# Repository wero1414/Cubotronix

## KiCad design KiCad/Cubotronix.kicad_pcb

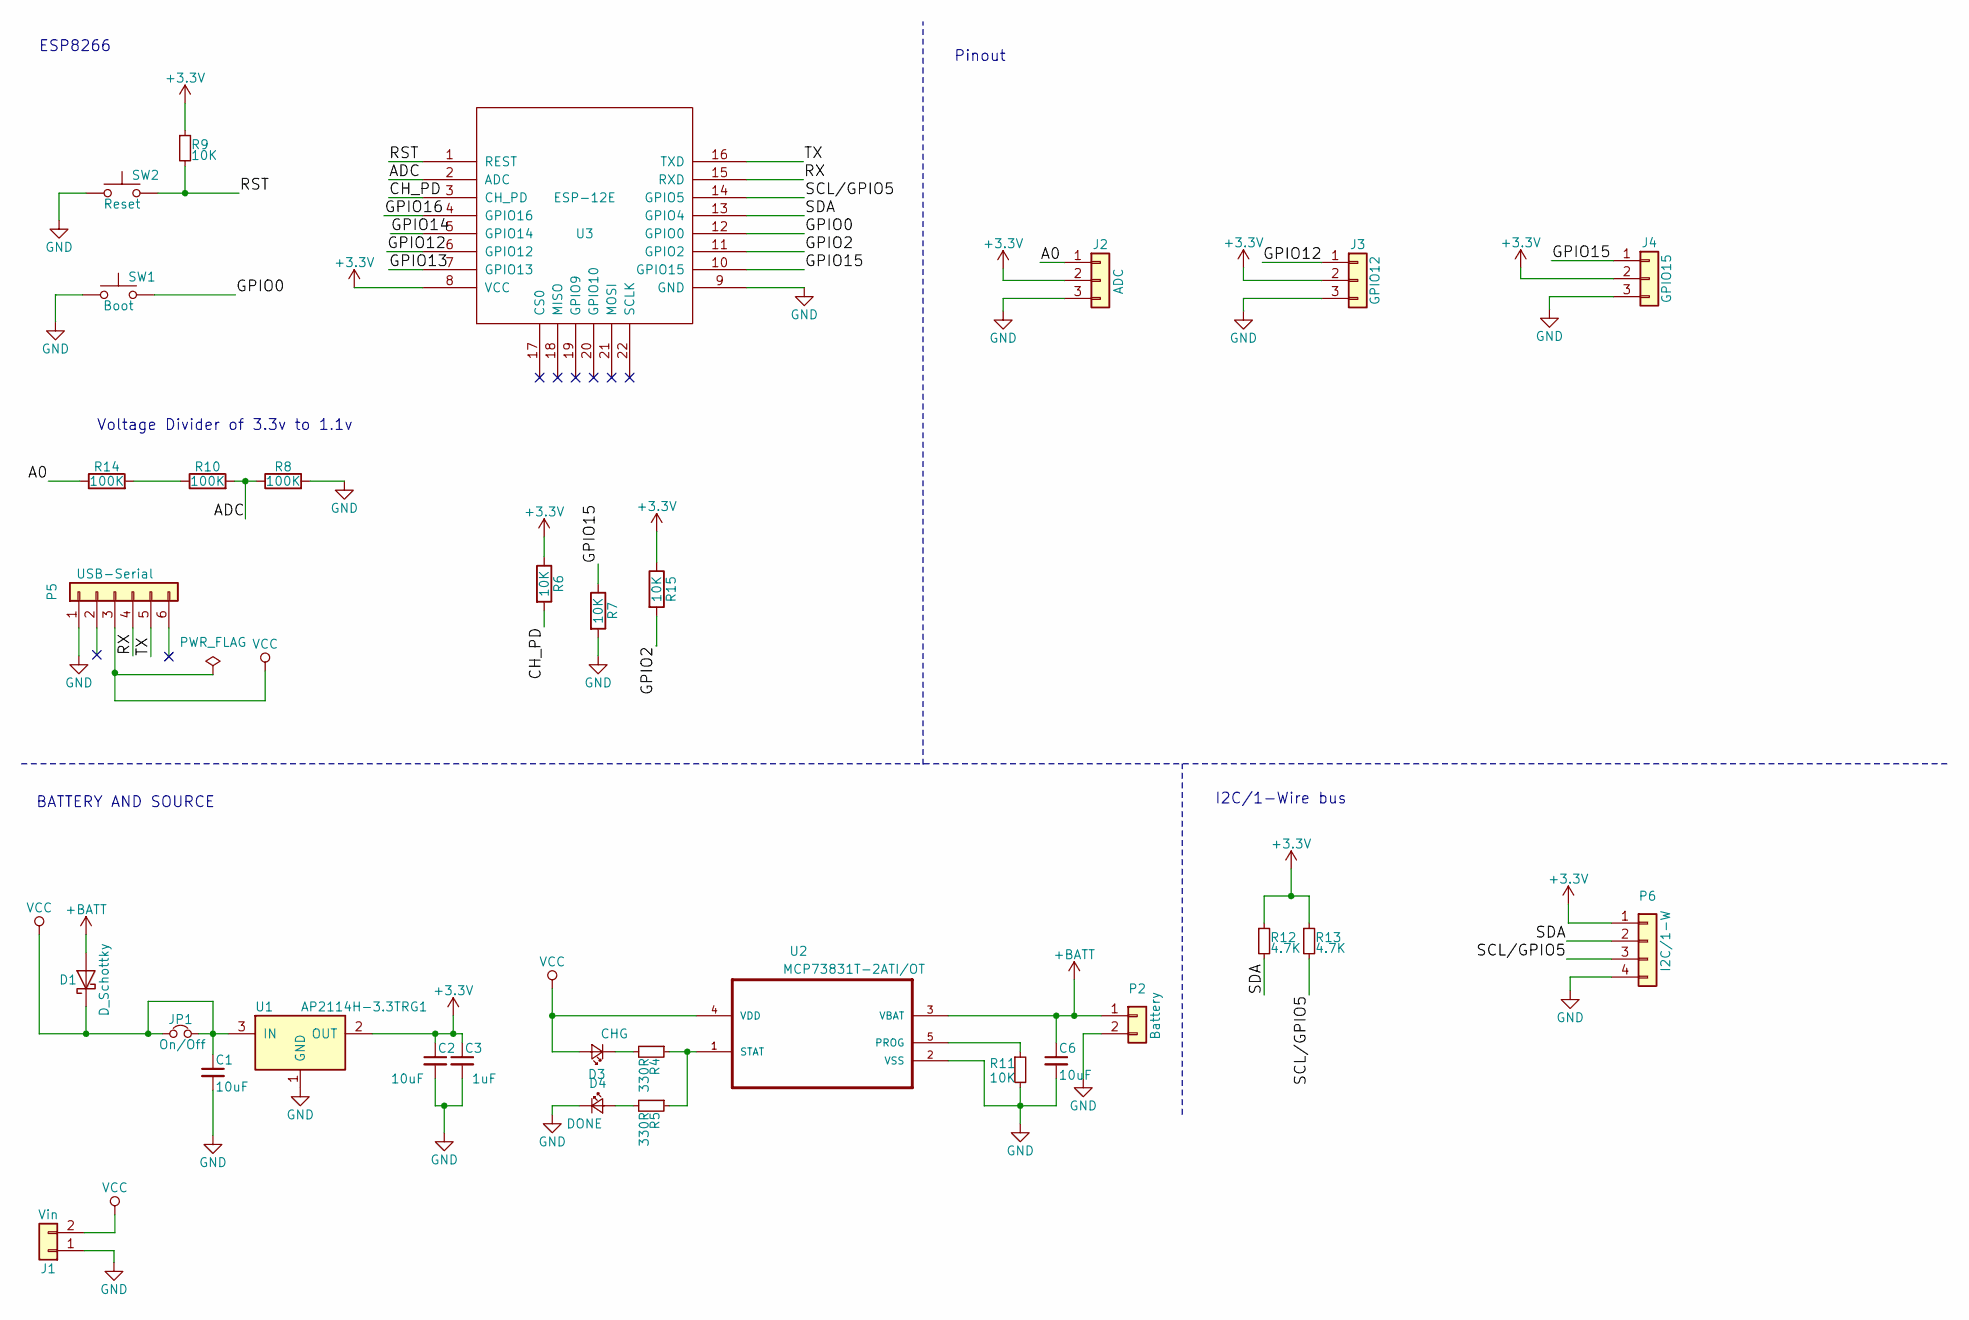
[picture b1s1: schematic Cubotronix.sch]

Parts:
C1, C2, C6: 10uF; C_0805_HandSoldering
C3: 1uF; C_0805_HandSoldering
D1: D_Schottky; SOD-123
D3: CHG; LED_0805
D4: DONE; LED_0805
J1: Vin; Pin_Header_Straight_1x02_Pitch2.54mm
J2: ADC; Pin_Header_Straight_1x03_Pitch2.54mm
J3: GPIO12; Pin_Header_Straight_1x03_Pitch2.54mm
J4: GPIO15; Pin_Header_Straight_1x03_Pitch2.54mm
JP1: On/Off; Pin_Header_Straight_1x02_Pitch2.54mm
P2: Battery; Pin_Header_Straight_1x02_Pitch2.54mm
P5: USB-Serial; Pin_Header_Straight_1x06_Pitch2.54mm
P6: I2C/1-W; Pin_Header_Straight_1x04_Pitch2.54mm
R4, R5: 330R; R_0805_HandSoldering
R6, R7, R9, R11, R15: 10K; R_0805_HandSoldering
R8, R10, R14: 100K; R_0805_HandSoldering
R12, R13: 4.7K; R_0805_HandSoldering
SW1: Boot; SW_SPST_B3U-1000P
SW2: Reset; SW_SPST_B3U-1000P
U1: AP2114H-3.3TRG1; SOT-223-3Lead_TabPin2
U2: MCP73831T-2ATI/OT; SOT-23-5
U3: ESP-12E; ESP-12E_SMD

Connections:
+3V3: C2.1, C3.1, J2.2, J3.2, J4.2, P6.1, R6.1, R9.1, R12.1, R13.1, R15.1, U1.2 (OUT), U3.8 (VCC)
+BATT: C6.1, D1.2 (A), P2.1, U2.3 (VBAT)
/A0: J2.1, R14.1
/ADC: R8.1, R10.2, U3.2 (ADC)
/CH_PD: R6.2, U3.3 (CH_PD)
/GPIO0: SW1.2, U3.12 (GPIO0)
/GPIO2: R15.2, U3.11 (GPIO2)
/GPIO12: J3.1, U3.6 (GPIO12)
/GPIO13: U3.7 (GPIO13)
/GPIO14: U3.5 (GPIO14)
/GPIO15: J4.1, R7.1, U3.10 (GPIO15)
/GPIO16: U3.4 (GPIO16)
/RST: R9.2, SW2.2, U3.1 (REST)
/RX: P5.4, U3.15 (RXD)
/SCL/GPIO5: P6.3, R13.2, U3.14 (GPIO5)
/SDA: P6.2, R12.2, U3.13 (GPIO4)
/TX: P5.5, U3.16 (TXD)
GND: C1.2, C2.2, C3.2, C6.2, D4.1 (K), J1.1, J2.3, J3.3, J4.3, P2.2, P5.1, P6.4, R7.2, R8.2, R11.2, SW1.1, SW2.1, U1.1 (GND), U2.2 (VSS), U3.9 (GND)
unnamed: D3.1 (K), R4.2
unnamed: D4.2 (A), R5.2
unnamed: R4.1, R5.1, U2.1 (STAT)
unnamed: R10.1, R14.2
unnamed: R11.1, U2.5 (PROG)
VCC: C1.1, D1.1 (K), D3.2 (A), J1.2, JP1.1, JP1.2, P5.3, U1.3 (IN), U2.4 (VDD)

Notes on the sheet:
ESP8266
BATTERY AND SOURCE
Voltage Divider of 3.3v to 1.1v
I2C/1-Wire bus
Pinout

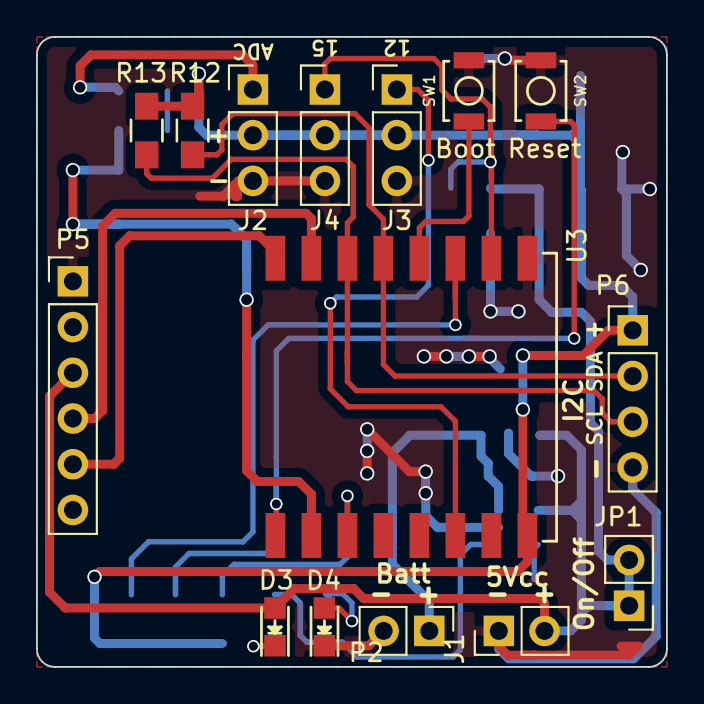
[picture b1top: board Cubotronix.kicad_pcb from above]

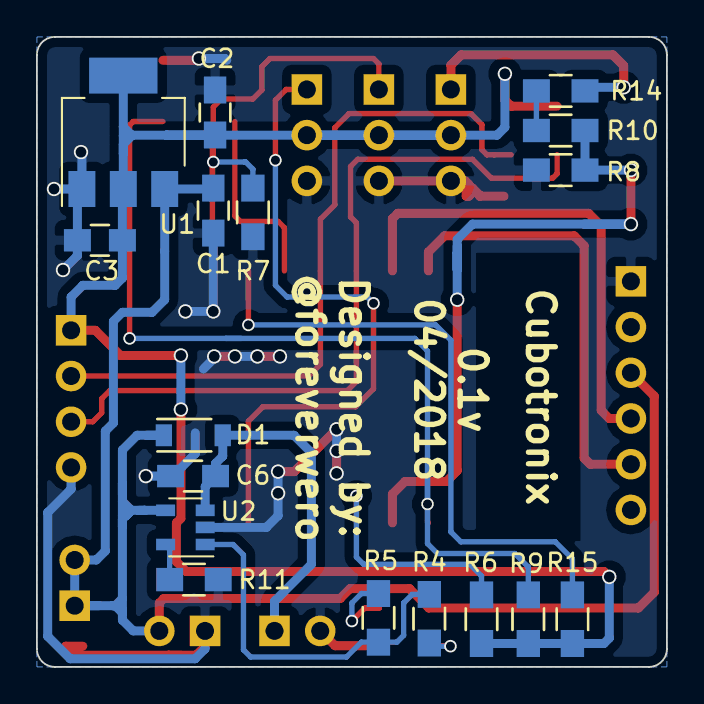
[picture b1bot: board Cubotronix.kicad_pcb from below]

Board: 2 copper layers, 35.0 x 35.0 mm, 32 parts (17 on the bottom side), 21 nets.

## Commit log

2018-04-18 add gitignore
2018-04-18 Added KiCad project
2018-04-18 Update of sch
2018-04-18 add labels to connectors
2018-04-18 Added schematic PDF
2018-04-19 Vias fixes
2018-04-22 change on/off pin
2018-04-22 Add labels
2018-04-25 add gerber
